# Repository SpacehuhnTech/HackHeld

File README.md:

# HackHeld

Here you can find all the hardware files for the HackHeld project. 

Visit [hackheld.spacehuhn.com](https://hackheld.spacehuhn.com) for more information.

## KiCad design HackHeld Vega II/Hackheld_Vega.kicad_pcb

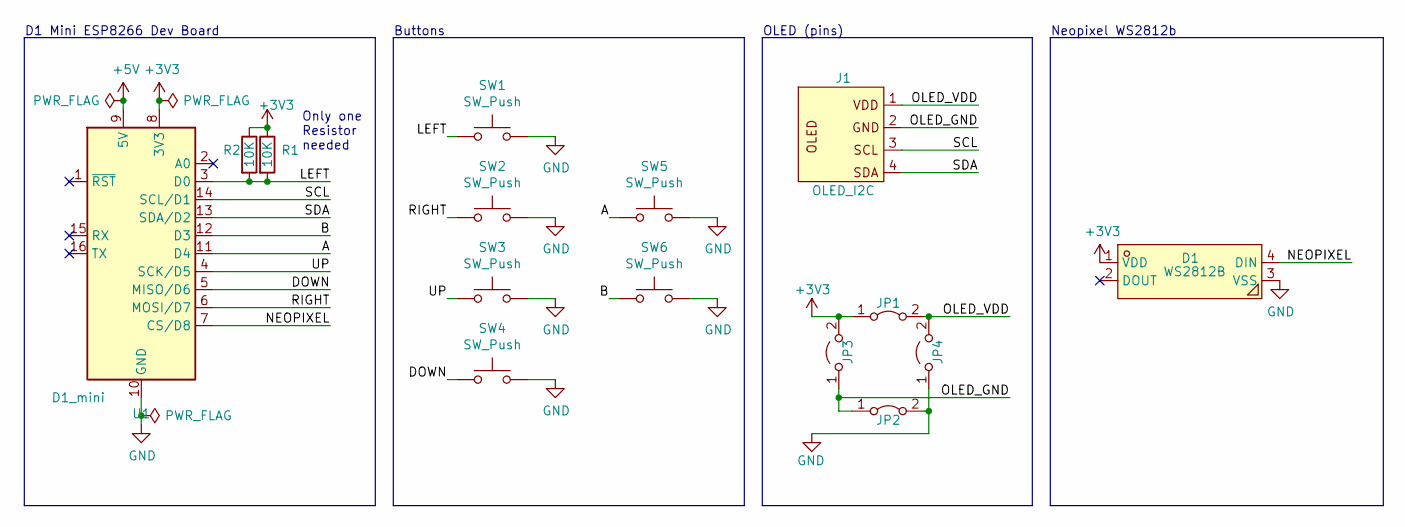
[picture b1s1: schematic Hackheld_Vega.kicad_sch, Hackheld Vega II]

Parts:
D1: WS2812B; LED-SMD_4P-L5.0-W5.0-BL_TC5050RGB-handsolder; MPN C114586
J1: OLED_I2C; OLED_I2C_1.3
JP1, JP2: Jumper_2_Bridged; Bridge
JP3, JP4: Jumper_2_Open; SolderJumper_Open
R1: 10K; R_1206_3216Metric_Pad1.30x1.75mm_HandSolder
R2: 10K; R_Axial_DIN0204_L3.6mm_D1.6mm_P7.62mm_Horizontal
SW1, SW2, SW3, SW4, SW6: SW_Push; SW-KEY-TH_4P-L6.0-W6.0-P4.50-LS6.5; MPN C381013; LCSC Part C381013
SW5: SW_Push; SW-KEY-TH_4P-L6.0-W6.0-P4.50-LS6.5; MPN C381013
U1: D1_mini; D1_mini_ESP8266

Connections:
+3V3: D1.1 (VDD), JP1.1 (A), JP3.2 (B), R1.1, R2.1, U1.8 (3V3)
+5V: U1.9 (5V)
/A: SW5.1 (A), U1.11 (D4)
/B: SW6.1 (A), U1.12 (D3)
/DOWN: SW4.1 (A), U1.5 (MISO/D6)
/LEFT: R1.2, R2.2, SW1.1 (A), U1.3 (D0)
/NEOPIXEL: D1.4 (DIN), U1.7 (CS/D8)
/OLED_GND: J1.2 (GND), JP2.1 (A), JP3.1 (A)
/OLED_VDD: J1.1 (VDD), JP1.2 (B), JP4.2 (B)
/RIGHT: SW2.1 (A), U1.6 (MOSI/D7)
/SCL: J1.3 (SCL), U1.14 (SCL/D1)
/SDA: J1.4 (SDA), U1.13 (SDA/D2)
/UP: SW3.1 (A), U1.4 (SCK/D5)
GND: D1.3 (VSS), JP2.2 (B), JP4.1 (A), SW1.2 (B), SW2.2 (B), SW3.2 (B), SW4.2 (B), SW5.2 (B), SW6.2 (B), U1.10 (GND)

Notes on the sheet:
OLED (pins)
D1 Mini ESP8266 Dev Board
Neopixel WS2812b
Buttons
Only one Resistor needed

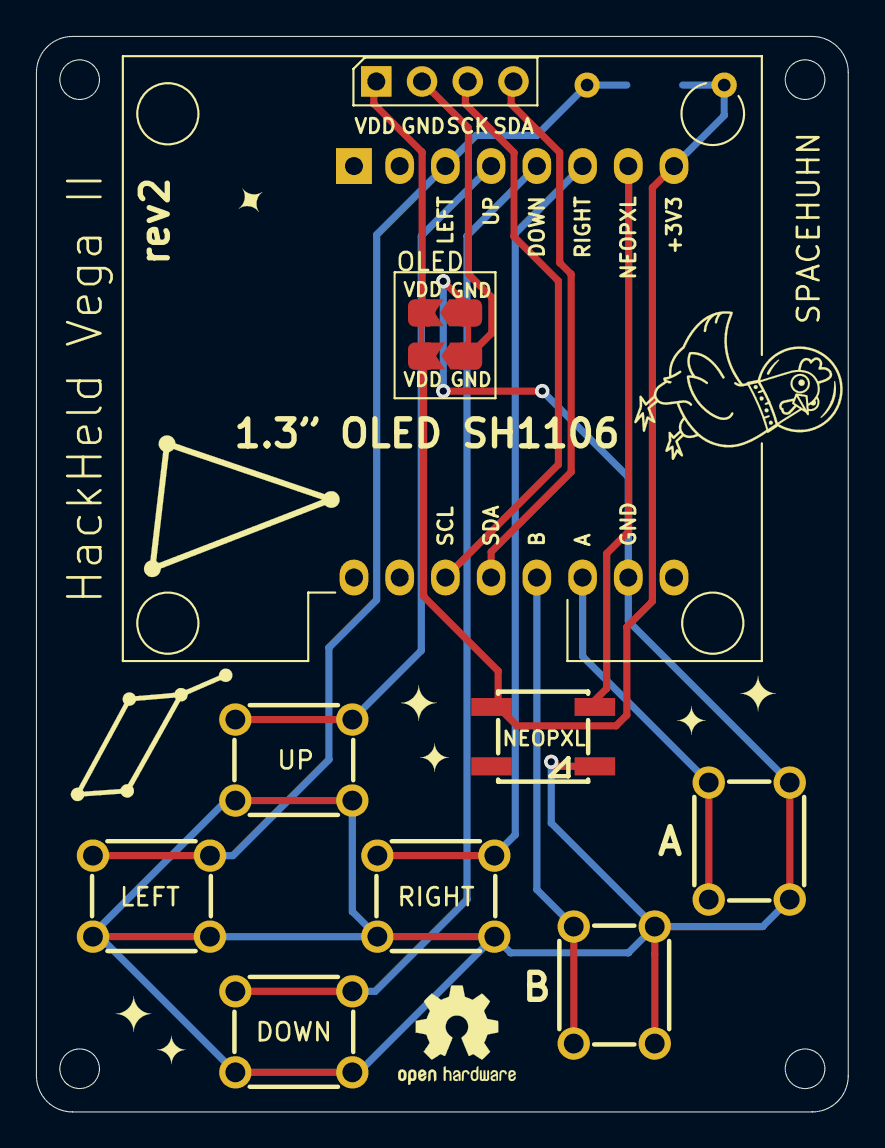
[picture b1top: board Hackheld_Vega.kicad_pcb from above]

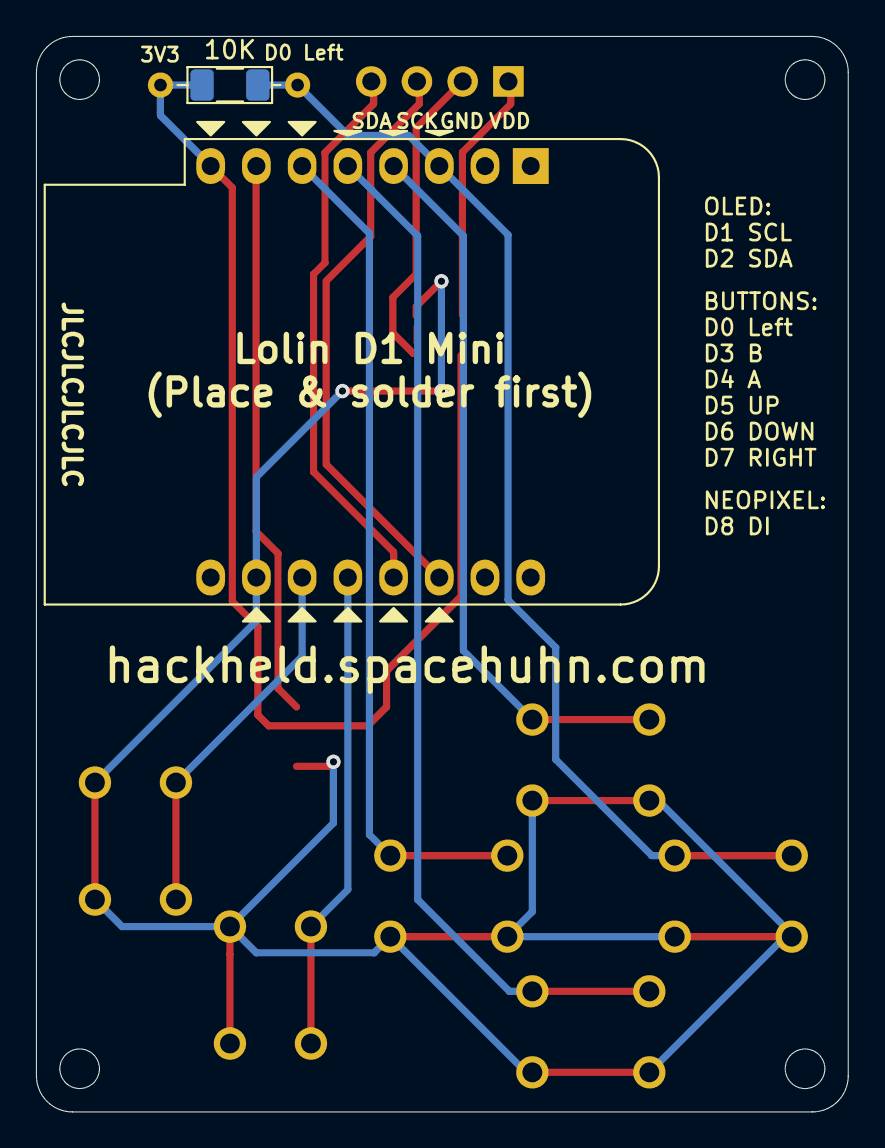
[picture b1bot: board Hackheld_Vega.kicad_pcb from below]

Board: 2 copper layers, 45.1 x 59.8 mm, 30 parts (3 on the bottom side), 13 nets.

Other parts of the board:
G3, G5, G7, G13: LOGO; star_tiny
G4, G6, G8: LOGO; star_small
G9: LOGO; lyra
G10: LOGO; summer_triangle
G11: OSHW-Logo2_7.3x6mm_SilkScreen
G14: LOGO; spacehuhn
REF1, REF2, REF3, REF4: MountingHole_2.2mm_M2

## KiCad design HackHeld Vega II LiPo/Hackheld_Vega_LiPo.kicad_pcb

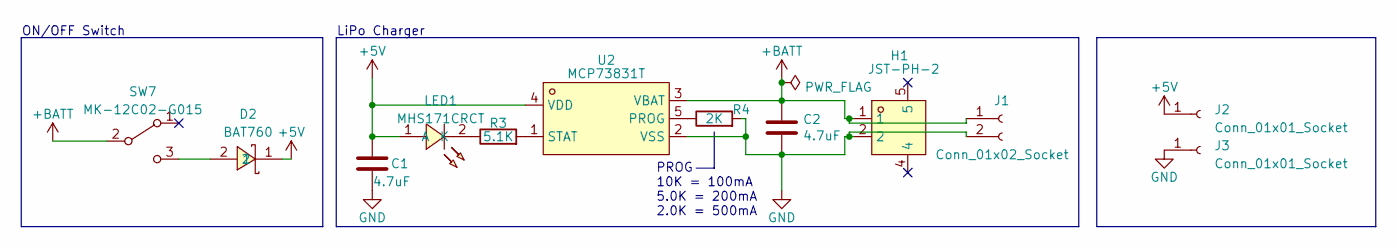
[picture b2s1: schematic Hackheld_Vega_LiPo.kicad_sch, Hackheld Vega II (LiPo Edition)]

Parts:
C1, C2: 4.7uF; C_0603_1608Metric
D2: BAT760; SOD-323_L1.8-W1.3-LS2.5-RD; MPN C116158
H1: JST-PH-2; CONN-SMD_2P-P2.00_XUNPU_WAFER-PH2.0-2PWB; MPN C3029440
J1: Conn_01x02_Socket; PinSocket_1x02_P2.54mm_Vertical
J2, J3: Conn_01x01_Socket; PinSocket_1x01_P2.54mm_Vertical
LED1: MHS171CRCT; LED-SMD_L2.0-W1.1_SIDE; MPN C693903
R3: 5.1K; R_0402_1005Metric
R4: 2K; R_0402_1005Metric
SW7: MK-12C02-G015; SW_MK-12C02-G020; MPN C2911519
U2: MCP73831T; SOT-23-5_L3.0-W1.7-P0.95-LS2.8-BL; MPN C424093

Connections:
+5V: C1.1, D2.1, J2.1, LED1.1 (A), U2.4 (VDD)
+BATT: C2.1, H1.1, J1.1, SW7.2 (B), U2.3 (VBAT)
GND: C1.2, C2.2, H1.2, J1.2, J3.1, R4.2, U2.2 (VSS)
unnamed: LED1.2 (K), R3.1
unnamed: D2.2, SW7.3 (C)
unnamed: R4.1, U2.5 (PROG)
unnamed: R3.2, U2.1 (STAT)

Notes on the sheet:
LiPo Charger
ON/OFF Switch
PROG 10K = 100mA 5.0K = 200mA 2.0K = 500mA

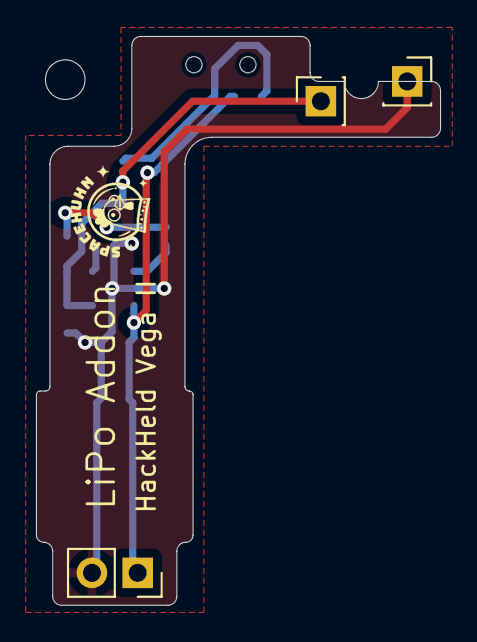
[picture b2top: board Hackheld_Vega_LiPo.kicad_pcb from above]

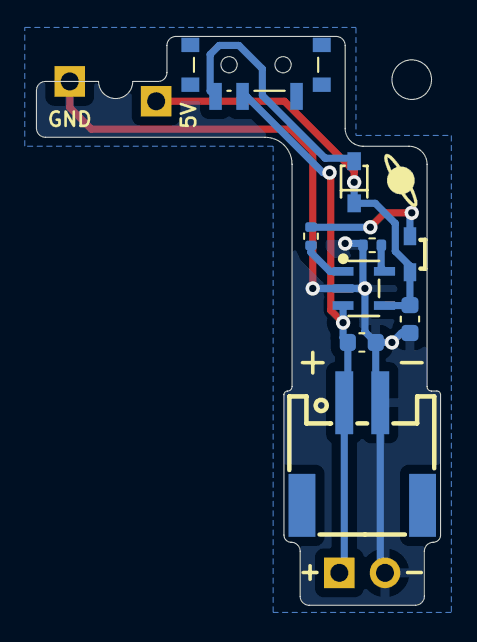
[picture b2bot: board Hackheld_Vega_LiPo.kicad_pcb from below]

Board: 2 copper layers, 22.4 x 31.6 mm, 16 parts (9 on the bottom side), 7 nets.

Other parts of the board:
REF1, REF2, REF3, REF4: MountingHole_2.2mm_M2

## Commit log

2021-08-06 So far so good
2021-08-06 PCB Download link
2021-08-06 Hackheld Vega Images
2021-08-07 Added Vega OLED note image
2021-11-01 removed redundant traces, removed <90deg trace angles, connected GND pours, alignment/centering of traces
2021-11-01 moved silk labels overlapping pads and silk overlapping neopxl footprint, added missing neopxl footprint to footprint directory
2021-11-01 updated gerber files
2021-11-03 Forgotten changes
    Looks like I made updates t the design without ever pushing it ¯\_(ツ)_/¯
2021-11-05 updated netlist, pcb and gerbers to reflect Stefan's change (swapping OLED connector's 3V3 and GND)
2021-11-27 Fix gerber files link
2022-05-18 change link to working one in README.md
    added https:// in one hyperlink so it would work correctly
2023-05-03 Move into sub folder
2023-05-03 HackHeld Vega II
2024-02-02 HackHeld Bat Mod PCB Files
